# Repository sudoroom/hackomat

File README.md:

# hack-o-mat vending machine

* so like the triac chips we tried, none of them were good enough for the motors in the vending machine.

* MOC3021 would work once and then fail closed, running the motor forever and smoking

* FOD420 did the same thing basically, although one of them worked a few times first

* TLP3023 never worked at all, probably because they're only rated for 100mA and died instantly

* not sure what part to try next

see https://sudoroom.org/wiki/Hack-o-mat

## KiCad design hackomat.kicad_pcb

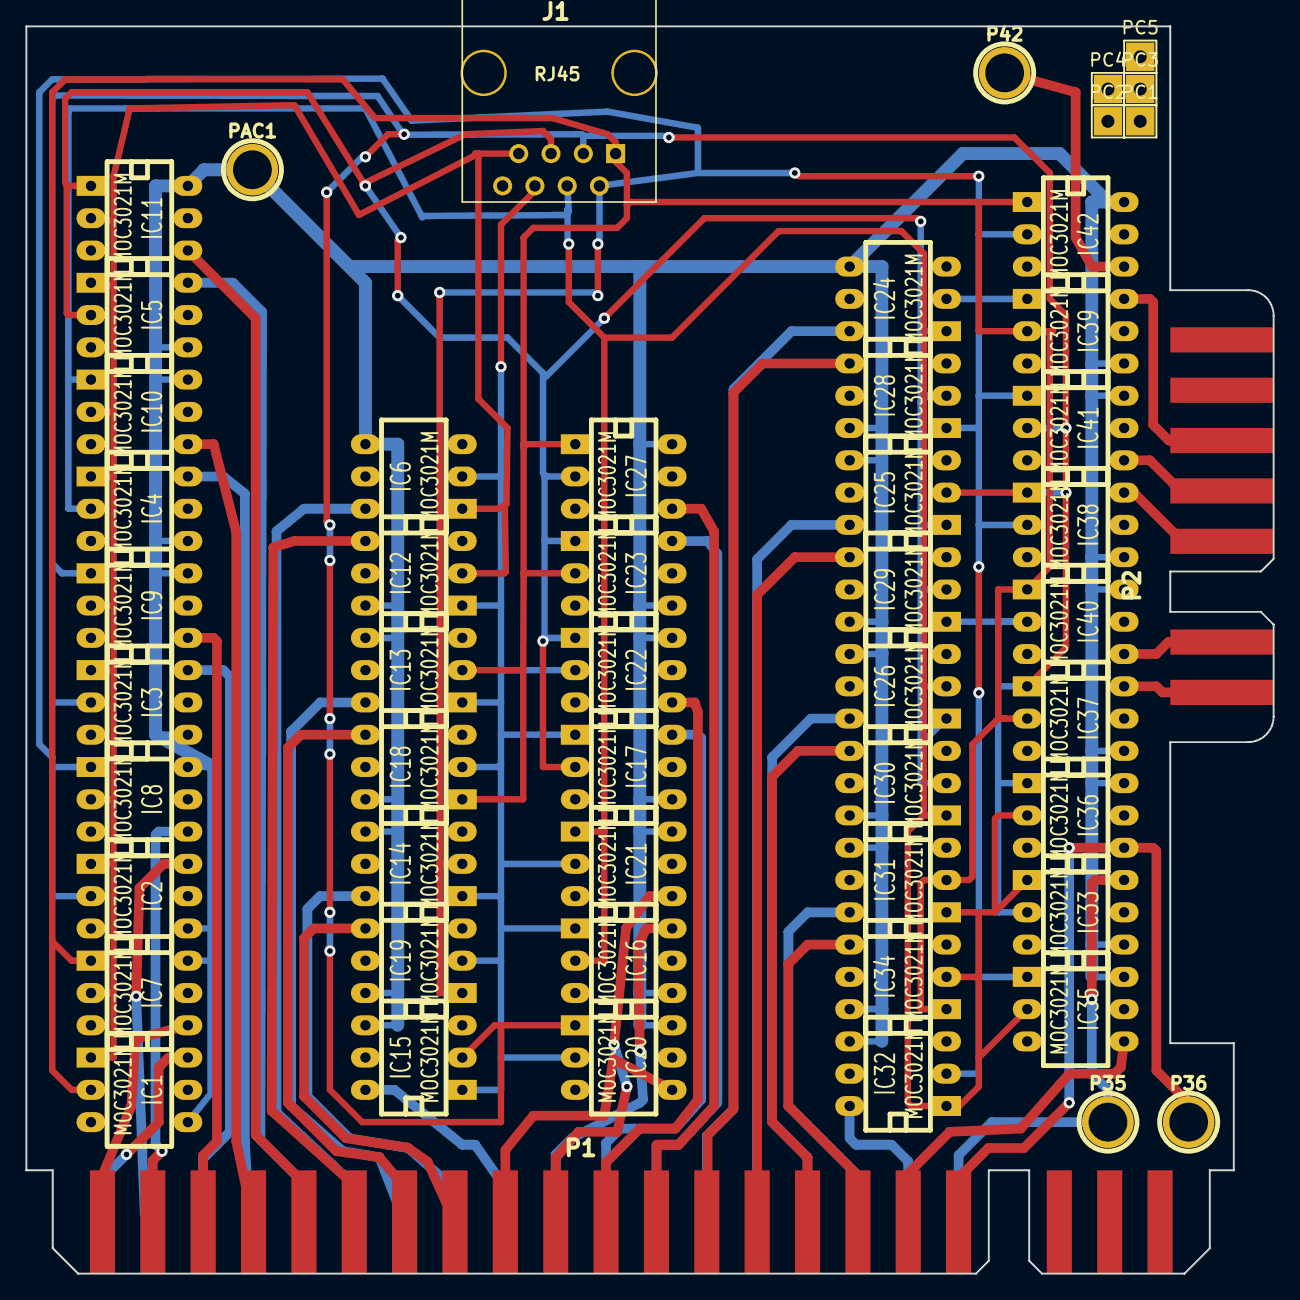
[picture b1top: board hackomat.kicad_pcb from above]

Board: 2 copper layers, 98.1 x 98.1 mm, 54 parts (0 on the bottom side), 55 nets.

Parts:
IC1, IC2, IC3, IC4, IC5, IC6, IC7, IC8, IC9, IC10, IC11, IC12, IC13, IC14, IC15, IC16, IC17, IC18, IC19, IC20, IC21, IC22, IC23, IC24, IC25, IC26, IC27, IC28, IC29, IC30, IC31, IC32, IC33, IC34, IC35, IC36, IC37, IC38, IC39, IC40, IC41, IC42: MOC3021M; DIP-6__300_ELL
J1: RJ45; RJ45_8
P1: CONN_02X22; euro44
P2: CONN_02X08; euro16
P35, P36, P42: CONN_01X01; 1pin
PAC1: CONN_01X01; 1pin
PC1, PC2, PC3, PC4, PC5: CONN_01X01; Pin_Header_Straight_1x01

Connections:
/a: IC1.2, IC7.1, IC13.2, IC18.1, IC23.2, IC27.1, IC31.2, IC34.1, IC37.2, IC39.2, IC40.1, IC42.1, J1.1
/ac: IC1.4, IC2.4, IC3.4, IC4.4, IC5.4, IC6.4, IC7.6, IC8.6, IC9.6, IC10.6, IC11.6, IC12.6, IC13.4, IC14.4, IC15.4, IC16.4, IC17.4, IC18.6, IC19.6, IC20.6, IC21.6, IC22.6, IC23.4, IC24.4, IC25.4, IC26.4, IC27.6, IC28.6, IC29.6, IC30.6, IC31.4, IC32.4, IC33.4, IC34.6, IC35.6, IC36.6, IC37.4, IC38.4, IC39.4, IC40.6, IC41.6, IC42.6, PAC1.1
/b: IC2.2, IC8.1, IC14.2, IC19.1, IC24.2, IC28.1, IC32.2, IC35.1, IC38.2, IC39.1, IC41.1, IC42.2, J1.2
/c: IC3.2, IC9.1, IC15.2, IC20.1, IC25.2, IC29.1, IC33.2, IC36.1, IC37.1, IC38.1, IC40.2, IC41.2, J1.3
/coin1: P2.7, PC1.1
/coin2: P2.9, PC2.1
/coin3: P2.11, PC3.1
/coin4: P2.13, PC4.1
/coin5: P2.15, PC5.1
/d: IC4.2, IC10.1, IC16.2, IC21.1, IC26.2, IC30.1, IC31.1, IC32.1, IC33.1, IC34.2, IC35.2, IC36.2, J1.4
/e: IC5.2, IC11.1, IC17.2, IC22.1, IC23.1, IC24.1, IC25.1, IC26.1, IC27.2, IC28.2, IC29.2, IC30.2, J1.5
/f: IC6.2, IC12.1, IC13.1, IC14.1, IC15.1, IC16.1, IC17.1, IC18.2, IC19.2, IC20.2, IC21.2, IC22.2, J1.6
/g: IC1.1, IC2.1, IC3.1, IC4.1, IC5.1, IC6.1, IC7.2, IC8.2, IC9.2, IC10.2, IC11.2, IC12.2, J1.7
/mo1: IC1.6, P1.1
/mo2: IC7.4, P1.2
/mo3: IC2.6, P1.3
/mo4: IC8.4, P1.4
/mo5: IC3.6, P1.5
/mo6: IC9.4, P1.6
/mo7: IC4.6, P1.7
/mo8: IC10.4, P1.8
/mo9: IC5.6, P1.9
/mo10: IC11.4, P1.10
/mo11: IC6.6, P1.11
/mo12: IC12.4, P1.12
/mo13: IC13.6, P1.13
/mo14: IC18.4, P1.14
/mo15: IC14.6, P1.15
/mo16: IC19.4, P1.16
/mo17: IC15.6, P1.17
/mo18: IC20.4, P1.18
/mo19: IC16.6, P1.19
/mo20: IC21.4, P1.20
/mo21: IC17.6, P1.21
/mo22: IC22.4, P1.22
/mo23: IC23.6, P1.23
/mo24: IC27.4, P1.24
/mo25: IC24.6, P1.25
/mo26: IC28.4, P1.26
/mo27: IC25.6, P1.27
/mo28: IC29.4, P1.28
/mo29: IC26.6, P1.29
/mo30: IC30.4, P1.30
/mo31: IC31.6, P1.31
/mo32: IC34.4, P1.32
/mo33: IC32.6, P1.33
/mo34: IC35.4, P1.34
/mo35: IC33.6, P1.35, P35.1
/mo36: IC36.4, P1.36, P36.1
/mo37: IC37.6, P2.2
/mo38: IC40.4, P2.4
/mo39: IC38.6, P2.8
/mo40: IC41.4, P2.10
/mo41: IC39.6, P2.12
/mo42: IC42.4, P42.1

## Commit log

2014-10-24 first commit of hackomat triac board
2014-10-24 make each triac have its own unique label on its leg
2014-10-24 add connectors and pins
2014-10-24 add documents relating to design, and .gitignore
2014-10-24 add example board-edge connector and a 44pin library symbol
2014-10-24 add schematic screenshot and README.md
2014-10-27 flipped over half the triacs since they never should have been flipped in the first place
2014-11-11 add euro connectors
2014-11-11 add project folder as footprints location
2014-11-11 set footprints for connectors in schematic
2014-11-11 put rounded corners onto euro16 connector
2014-12-11 cut corners and added line end notes to euro44
2014-12-11 change board edge lines from layer F.SilkS to Edge.Cuts on euro44
2014-12-11 add line end notes to euro16
2014-12-11 add pcboard with connectors and edges in place
2014-12-11 move edge connectors to make entire board under 100x100mm
2014-12-11 change PC1-PC5 to have smaller pinhole footprints
2014-12-11 place all triacs and other parts on board in order
2014-12-11 add image of unwired board
2014-12-11 move triacs to a more sensible, more sequential arrangement
2014-12-12 update README.md with link to sudoroom wiki page
2014-12-13 wire up about half the AC wires to triacs
2014-12-14 almost all the rj45 data pins, all the other traces
2014-12-14 we are having fun
2014-12-14 board is finished thanx to substack
2014-12-14 fixed some white lines, then rayc touched it, watch out
2015-05-09 add datasheet for 2 amp 5ma-triggered triacs
2019-04-25 update README.md with triac problems
2019-04-25 thanks rab for this part suggestion
